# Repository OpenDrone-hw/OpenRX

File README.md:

# OpenRX

OpenRX is the home of the OpenDrone open-source ExpressLRS receiver family.
The four boards now follow the same one-board-per-repository standard as the
rest of the OpenDrone hardware line. This repository remains open as the
family hub, preserving its stars, issues, releases, tags, and complete history.

## Board repositories

| Board | Radio and antenna | Source and releases |
|---|---|---|
| OpenRX Lite | SX1281, 2.4 GHz, on-board ceramic | [OpenDrone-hw/OpenRX-Lite](https://github.com/OpenDrone-hw/OpenRX-Lite) |
| OpenRX Lite-UFL | SX1281, 2.4 GHz, U.FL | [OpenDrone-hw/OpenRX-Lite-UFL](https://github.com/OpenDrone-hw/OpenRX-Lite-UFL) |
| OpenRX Mono | LR1121, dual band, one U.FL | [OpenDrone-hw/OpenRX-Mono](https://github.com/OpenDrone-hw/OpenRX-Mono) |
| OpenRX Gemini | Two LR1121 radios, dual band, two U.FL | [OpenDrone-hw/OpenRX-Gemini](https://github.com/OpenDrone-hw/OpenRX-Gemini) |

KiCad sources, firmware target definitions, board documentation, and future
releases live in those repositories. The family-level Rev 2 and Rev 2.1 tags
and releases remain here as the immutable record of the original combined
repository; their per-board assets are also available from each board repo.
The Rev 2.2 tag marks the source of the production panel in `panel/`, the four
boards merged on one strip. Fab-ready manufacturing files are kept in a private
Incutec production repository and are not published.

## Specifications

| | Lite | Lite-UFL | Mono | Gemini |
|---|---|---|---|---|
| Band | 2.4 GHz | 2.4 GHz | Dual band | Dual band, Xrossband |
| Radio | SX1281 | SX1281 | LR1121 | 2x LR1121 |
| Antenna | On-board ceramic | U.FL | U.FL | 2x U.FL |
| Telemetry power | 13 dBm (20 mW) | 13 dBm (20 mW) | Up to 22 dBm (158 mW) | Up to 22 dBm (158 mW) |
| Protocol | CRSF | CRSF | CRSF | CRSF |
| MCU | ESP32-C3 | ESP32-C3 | ESP32-C3 | ESP32-C3 |
| Input | 5 V pad | 5 V pad | 5 V pad | 5 V pad |
| Firmware | ExpressLRS | ExpressLRS | ExpressLRS | ExpressLRS |
| Flashing | Betaflight passthrough or Wi-Fi | Betaflight passthrough or Wi-Fi | Betaflight passthrough or Wi-Fi | Betaflight passthrough or Wi-Fi |
| Dimensions | 10.0 x 11.5 mm | 10.0 x 11.5 mm | 10.0 x 17.3 mm | 17.0 x 15.7 mm |
| PCB | 6-layer, 1.0 mm | 6-layer, 1.0 mm | 6-layer, 1.0 mm | 6-layer, 1.0 mm |

OSHWA certification is issued per board:
[Lite BE000030](https://certification.oshwa.org/be000030.html),
[Lite-UFL BE000031](https://certification.oshwa.org/be000031.html),
[Mono BE000032](https://certification.oshwa.org/be000032.html), and
[Gemini BE000033](https://certification.oshwa.org/be000033.html).

## In the line

What pairs with what, and what is available:
[opendrone.be](https://opendrone.be).

## Contributing

Choose the board repository above for hardware changes. Family-wide questions
and historical discussion remain welcome here. See
[CONTRIBUTING.md](CONTRIBUTING.md).

## License

Hardware licensed under [CERN-OHL-S-2.0](https://ohwr.org/cern_ohl_s_v2.txt),
see [LICENSE](LICENSE).

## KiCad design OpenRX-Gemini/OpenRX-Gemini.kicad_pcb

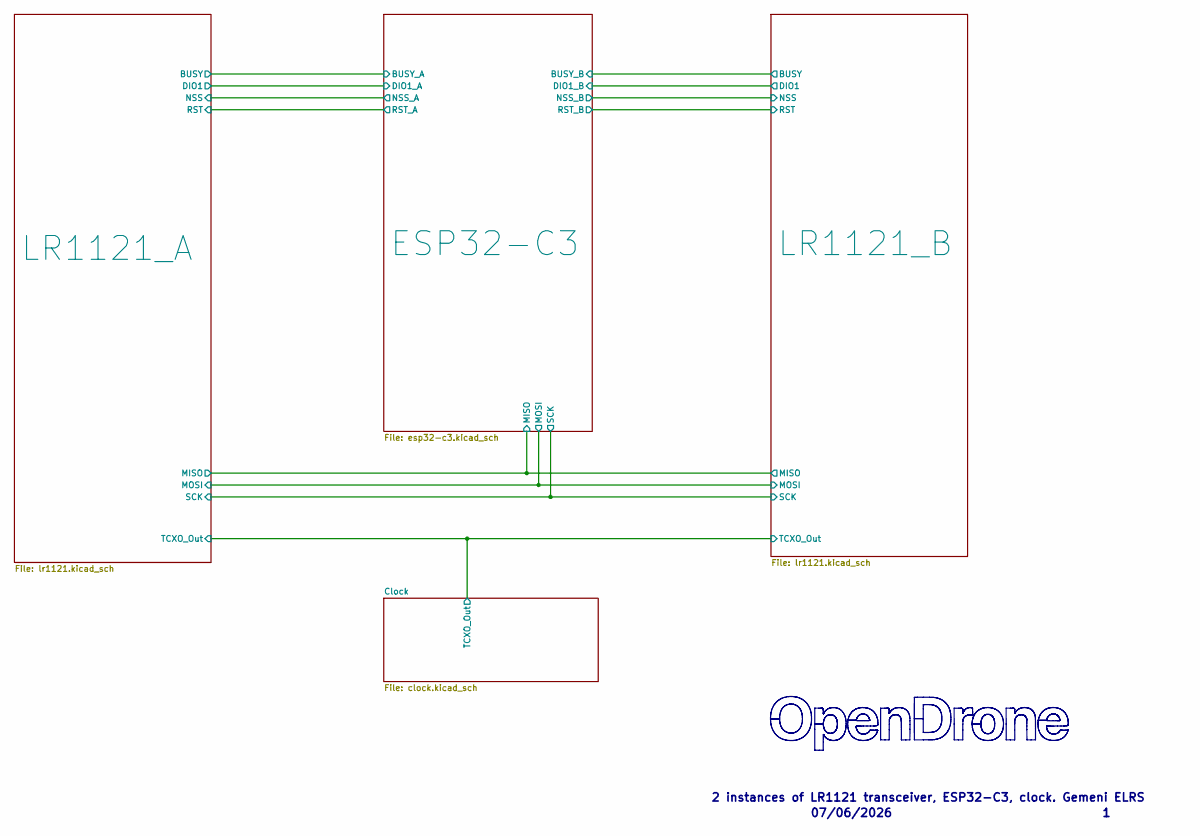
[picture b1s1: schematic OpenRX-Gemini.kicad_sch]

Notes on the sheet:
07/06/2026
2 instances of LR1121 transceiver, ESP32-C3, clock. Gemeni ELRS

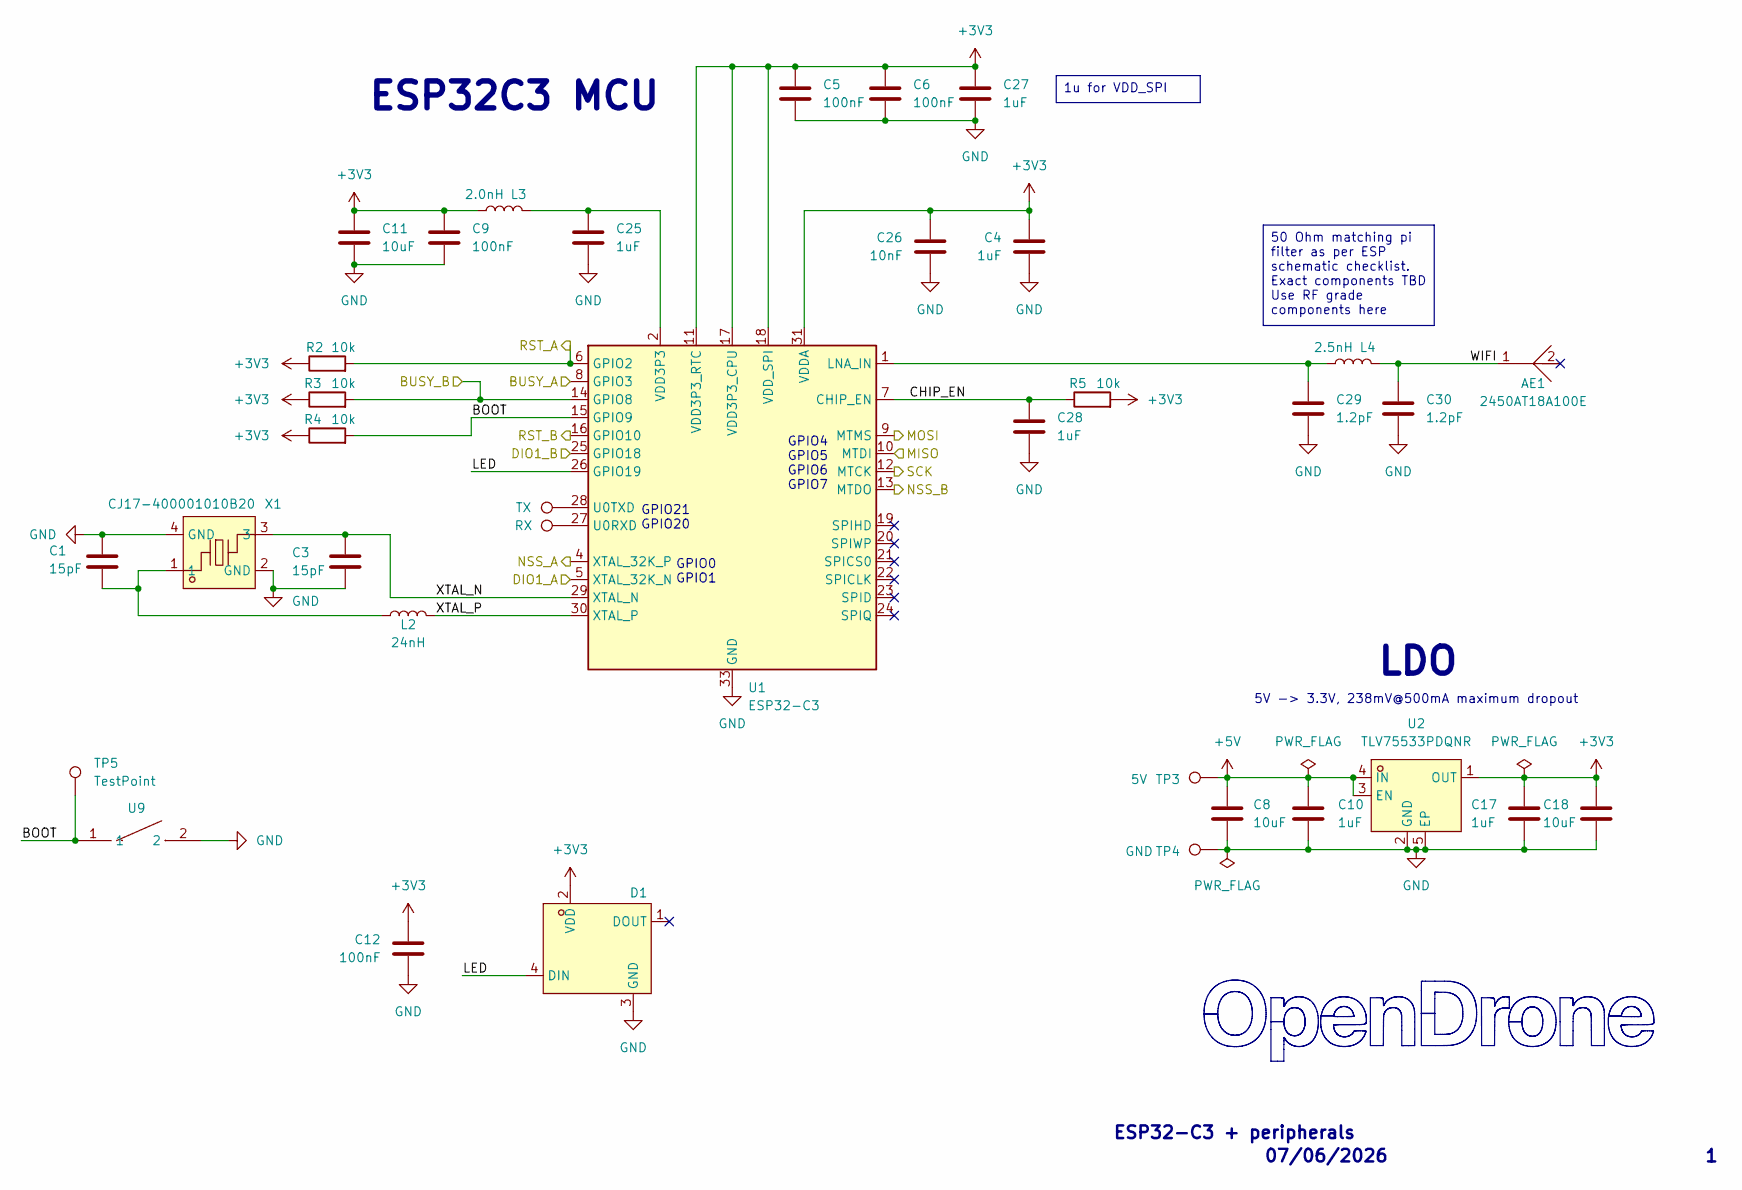
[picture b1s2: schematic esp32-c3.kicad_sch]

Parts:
AE1: 2450AT18A100E; ANT-SMD_L3.2-W1.6; MPN 2450AT18A100E; LCSC Part C89334
C1, C3: 15pF; C_0201_0603Metric; MPN GRM0335C1H150JA01D; LCSC C85891
C4, C10, C17, C25, C27, C28: 1uF; C_0201_0603Metric; MPN GRM033R61A105ME44D; LCSC C76935
C5, C6, C9, C12: 100nF; C_0201_0603Metric; MPN GRM033R61E104KE14D; LCSC C76939
C8, C18: 10uF; C_0402_1005Metric; MPN CL05A106MQ5NUNC; LCSC C15525
C11: 10uF; C_0402_1005Metric; MPN GRM155R60J106ME44D; LCSC C76991
C26: 10nF; C_0201_0603Metric; MPN GRM033R61A103KA01J; LCSC C2168164
C29, C30: 1.2pF; C_0201_0603Metric; MPN GRM0335C1H1R2BA01D; LCSC C85895
D1: XL-1010RGBC-WS2812B; LED-SMD_4P-L1.0-W1.0-TL_XL-1010RGBC-WS2812B; MPN XL-1010RGBC-2812B; LCSC C5349953
L2: 24nH; L_0201_0603Metric; MPN LQP03TN24NH02D; LCSC C206441
L3: 2.0nH; L_0201_0603Metric; MPN LQP03TN2N0B02D; LCSC C86125
L4: 2.5nH; L_0201_0603Metric; MPN LQP03TN2N5C02D; LCSC C206435
R2, R3, R4, R5: 10k; R_0201_0603Metric; MPN RC0201FR-0710KL; LCSC C106225
TP1: RX; SolderPad_1.2x2.0mm
TP2: TX; SolderPad_1.2x2.0mm
TP3: 5V; SolderPad_1.2x2.0mm
TP4: GND; SolderPad_1.2x2.0mm
TP5: TestPoint; TestPoint_Pad_D1.5mm
U1: ESP32-C3; QFN-32-1EP_5x5mm_P0.5mm_EP3.7x3.7mm
U2: TLV75533PDQNR; X2SON-4_L1.0-W1.0-P0.65-TL-EP; MPN TLV75533PDQNR; LCSC Part C2861882
U9: TS2306A 240GF MSM 9_C2976675; SW-SMD_4P-L3.0-W2.0-P0.85-LS3.5; MPN TS2306A 240gf MSM 9; LCSC C2976675
X1: CJ17-400001010B20; CRYSTAL-SMD_4P-L1.6-W1.2-BL; MPN CJ17-400001010B20; LCSC Part C2875272

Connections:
+3V3: C4.1, C5.1, C6.1, C9.1, C11.1, C12.1, C17.1, C18.1, C26.1, C27.1, D1.2 (VDD), L3.2, R2.1, R3.1, R4.1, R5.2, U1.11 (VDD3P3_RTC), U1.17 (VDD3P3_CPU), U1.18 (VDD_SPI), U1.31 (VDDA), U1.32 (VDDA), U2.1 (OUT); also elsewhere on the board
+5V: C8.1, C10.1, TP3.1 (1_1), U2.3 (EN), U2.4 (IN)
/ESP32-C3/BOOT: R4.2, TP5.1 (1_1), U1.15 (GPIO9), U9.1
/ESP32-C3/BUSY_A: U1.8 (GPIO3); also elsewhere on the board
/ESP32-C3/BUSY_B: R3.2, U1.14 (GPIO8); also elsewhere on the board
/ESP32-C3/CHIP_EN: C28.1, R5.1, U1.7 (CHIP_EN)
/ESP32-C3/DIO1_A: U1.5 (XTAL_32K_N); also elsewhere on the board
/ESP32-C3/DIO1_B: U1.25 (GPIO18); also elsewhere on the board
/ESP32-C3/LED: D1.4 (DIN), U1.26 (GPIO19)
/ESP32-C3/MISO: U1.10 (MTDI); also elsewhere on the board
/ESP32-C3/MOSI: U1.9 (MTMS); also elsewhere on the board
/ESP32-C3/NSS_A: U1.4 (XTAL_32K_P); also elsewhere on the board
/ESP32-C3/NSS_B: U1.13 (MTDO); also elsewhere on the board
/ESP32-C3/RST_A: R2.2, U1.6 (GPIO2); also elsewhere on the board
/ESP32-C3/RST_B: U1.16 (GPIO10); also elsewhere on the board
/ESP32-C3/SCK: U1.12 (MTCK); also elsewhere on the board
/ESP32-C3/WIFI: AE1.1, C30.1, L4.1
/ESP32-C3/XTAL_N: C3.1, U1.29 (XTAL_N), X1.3
/ESP32-C3/XTAL_P: L2.2, U1.30 (XTAL_P)
GND: C1.2, C3.2, C4.2, C5.2, C6.2, C8.2, C9.2, C10.2, C11.2, C12.2, C17.2, C18.2, C25.2, C26.2, C27.2, C28.2, C29.2, C30.2, D1.3 (GND), TP4.1 (1_1), U1.33 (GND), U2.2 (GND), U2.5 (EP), U9.2, X1.2 (GND), X1.4 (GND); also elsewhere on the board
unnamed: C1.1, L2.1, X1.1
unnamed: C25.1, L3.1, U1.2 (VDD3P3), U1.3 (VDD3P3)
unnamed: C29.1, L4.2, U1.1 (LNA_IN)
unnamed: TP1.1 (1_1), U1.27 (U0RXD)
unnamed: TP2.1 (1_1), U1.28 (U0TXD)

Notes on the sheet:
ESP32C3 MCU
07/06/2026
GPIO21 GPIO20
GPIO0 GPIO1
5V -> 3.3V, 238mV@500mA maximum dropout
GPIO4 GPIO5 GPIO6 GPIO7
LDO
ESP32-C3 + peripherals
50 Ohm matching pi filter as per ESP schematic checklist. Exact components TBD Use RF grade components here
1u for VDD_SPI

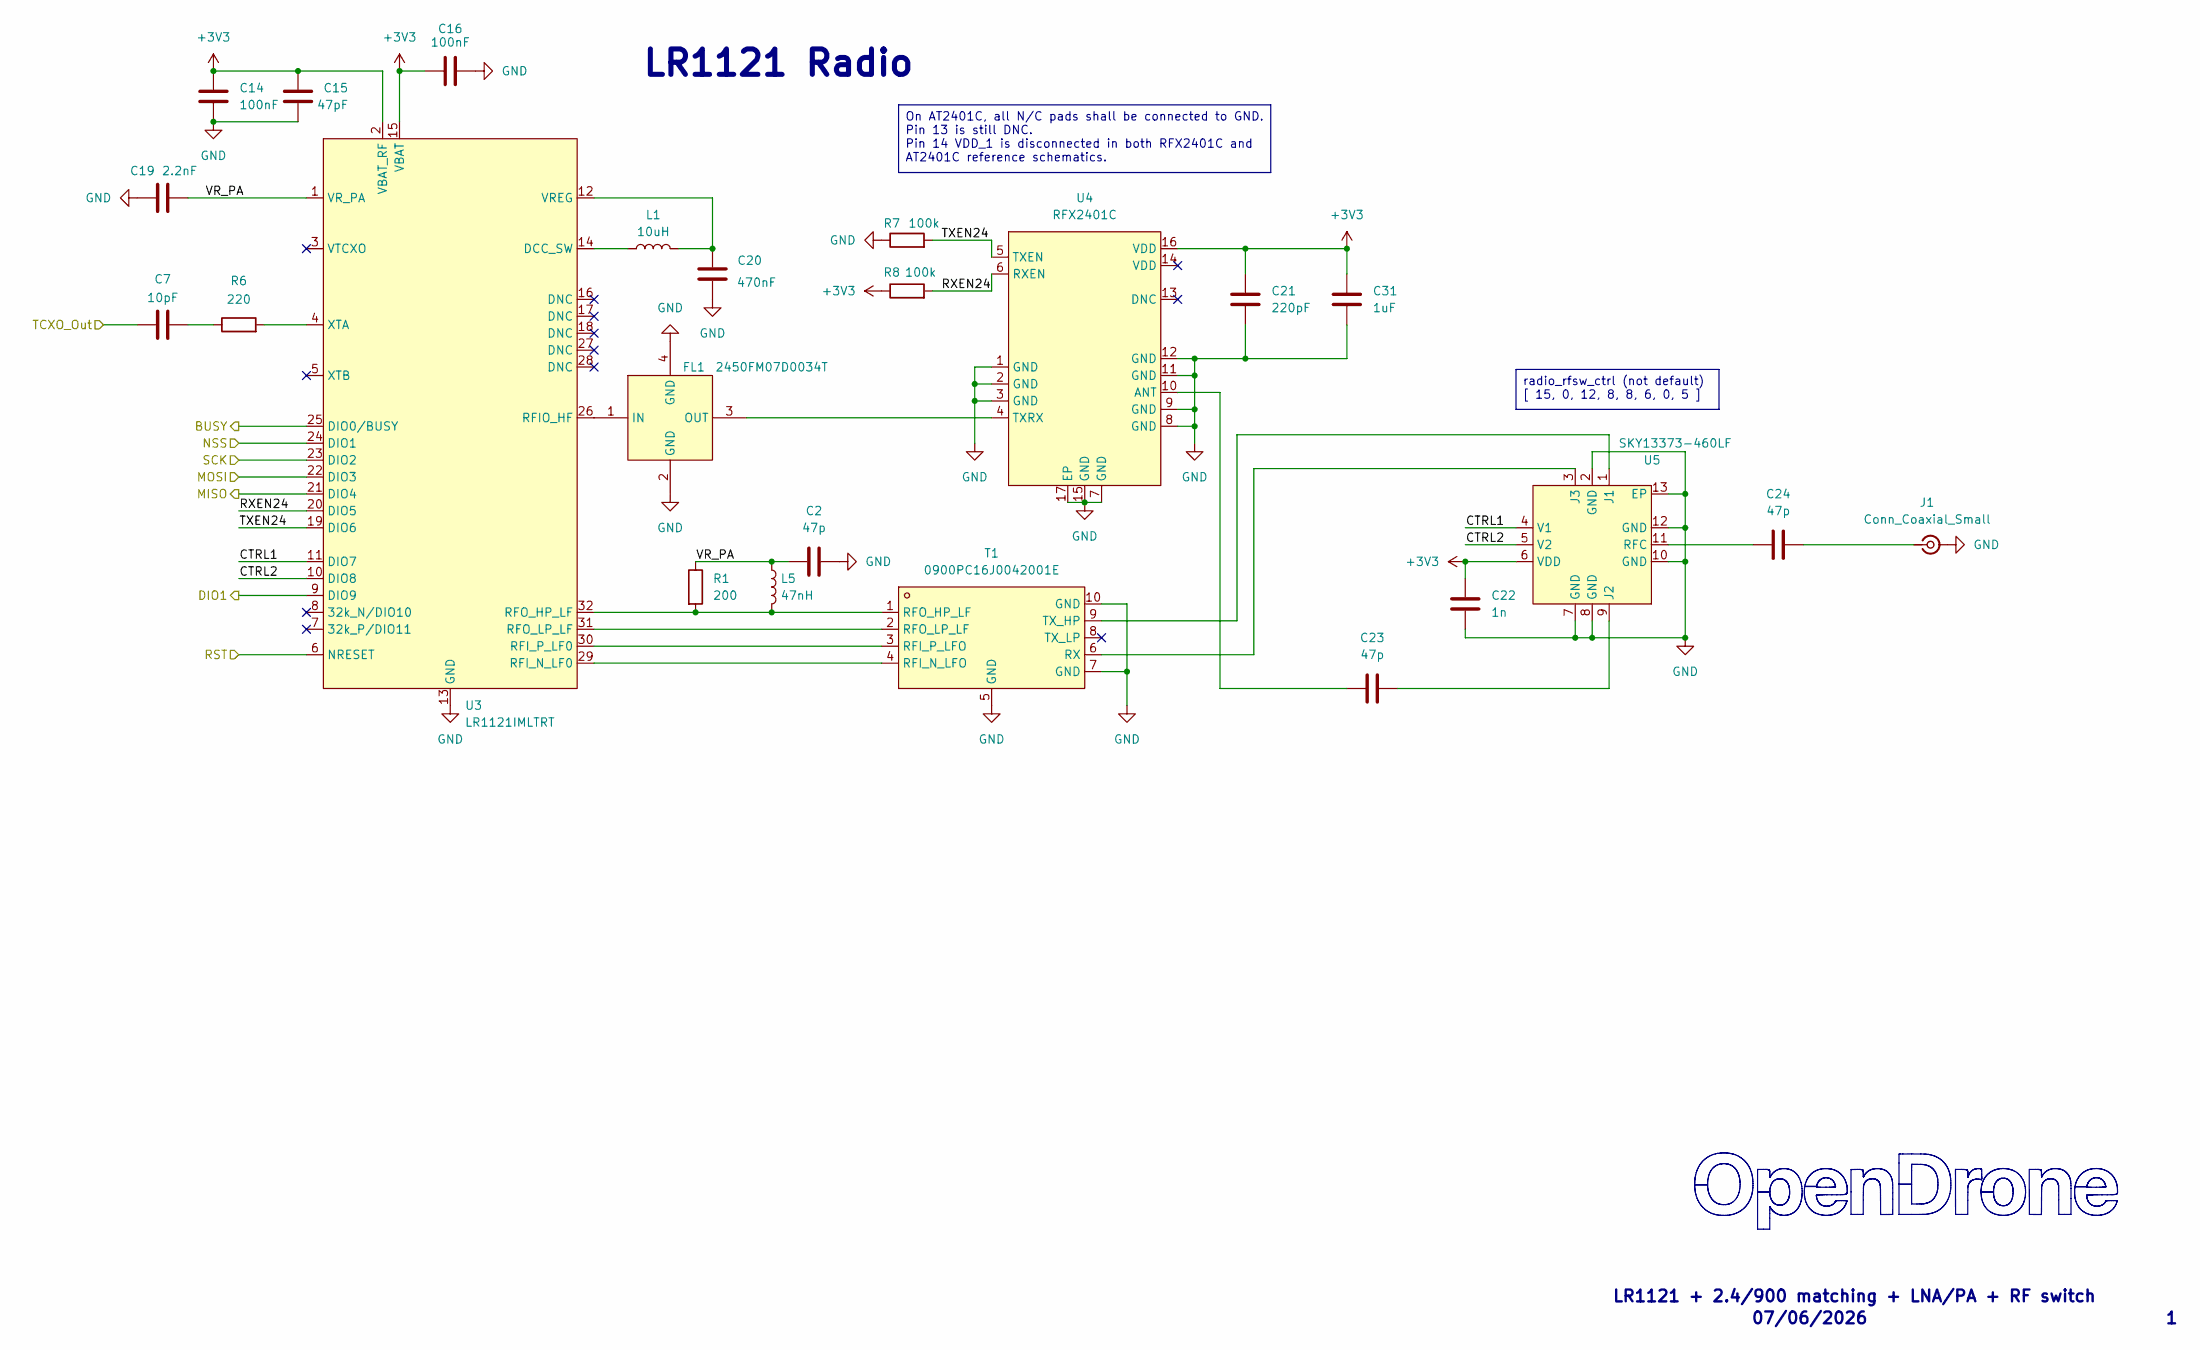
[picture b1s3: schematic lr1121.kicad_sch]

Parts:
C2, C23, C24: 47p; C_0201_0603Metric; MPN GRM0335C1H470JA01D; LCSC C85908
C7: 10pF; C_0201_0603Metric; MPN GRM0335C1H100FA01D; LCSC C384956
C14, C16: 100nF; C_0201_0603Metric; MPN GRM033R61E104KE14D; LCSC C76939
C15: 47pF; C_0201_0603Metric; MPN GRM0335C1H470JA01D; LCSC C85908
C19: 2.2nF; C_0201_0603Metric; MPN GRM033R71E222KA12D; LCSC C161488
C20: 470nF; C_0201_0603Metric; MPN GRM033R60J474KE90D; LCSC C85926
C21: 220pF; C_0201_0603Metric; MPN GRM0335C1E221JA01D; LCSC C907939
C22: 1n; C_0201_0603Metric; MPN GRM033R71H102KA12D; LCSC C85934
C31: 1uF; C_0201_0603Metric; MPN GRM033R61A105ME44D; LCSC C76935
FL1: 2450FM07D0034T; FILTER-SMD_4P-L1.0-W0.5-L; MPN 2450FM07D0034T; LCSC Part_1 C2651081
J1: Conn_Coaxial_Small; U.FL_Hirose_U.FL-R-SMT-1_Vertical; MPN U.FL-R-SMT-1(80); LCSC C88374
L1: 10uH; L_0603_1608Metric; MPN MLZ1608N100LT000; LCSC C194437
L5: 47nH; L_0402_1005Metric; MPN LQW15AN47NJ00D; LCSC C192855
R1: 200; R_0201_0603Metric; MPN RC0201FR-07200RL; LCSC C274337
R6: 220; R_0201_0603Metric; MPN ERJ-1GNF2200C; LCSC C2074788
R7, R8: 100k; R_0201_0603Metric; MPN RC0201FR-07100KL; LCSC C106224
T1: 0900PC16J0042001E; FILTER-SMD_10P-L2.0-W1.6-BL; MPN 0900PC16J0042001E; LCSC C19842466
U3: LR1121IMLTRT; QFN-32-1EP_5x5mm_P0.5mm_EP3.7x3.7mm; MPN LR1121IMLTRT; LCSC C7498014
U4: RFX2401C; QFN-16_L3.0-W3.0-P0.50-BL-EP1.7; MPN RFX2401C; LCSC C19213
U5: SKY13373-460LF; QFN-12_EP_2x2_Pitch0.5mm

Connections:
+3V3: C14.1, C15.1, C16.1, C21.1, C22.1, C31.1, R8.1, U3.2 (VBAT_RF), U3.15 (VBAT), U4.16 (VDD), U5.6 (VDD); also elsewhere on the board
/Clock/TCXO_Out: C7.2; also elsewhere on the board
/ESP32-C3/BUSY_A: U3.25 (DIO0/BUSY); also elsewhere on the board
/ESP32-C3/DIO1_A: U3.9 (DIO9); also elsewhere on the board
/ESP32-C3/MISO: U3.21 (DIO4); also elsewhere on the board
/ESP32-C3/MOSI: U3.22 (DIO3); also elsewhere on the board
/ESP32-C3/NSS_A: U3.24 (DIO1); also elsewhere on the board
/ESP32-C3/RST_A: U3.6 (NRESET); also elsewhere on the board
/ESP32-C3/SCK: U3.23 (DIO2); also elsewhere on the board
/LR1121_A/CTRL1: U3.11 (DIO7), U5.4 (V1)
/LR1121_A/CTRL2: U3.10 (DIO8), U5.5 (V2)
/LR1121_A/RXEN24: R8.2, U3.20 (DIO5), U4.6 (RXEN)
/LR1121_A/TXEN24: R7.2, U3.19 (DIO6), U4.5 (TXEN)
/LR1121_A/VR_PA: C2.1, C19.1, L5.1, R1.1, U3.1 (VR_PA)
GND: C2.2, C14.2, C15.2, C16.2, C19.2, C20.1, C21.2, C22.2, C31.2, FL1.2 (GND), FL1.4 (GND), J1.2 (Ext), R7.1, T1.5 (GND), T1.7 (GND), T1.10 (GND), U3.13 (GND), U3.33 (EP), U4.1 (GND), U4.2 (GND), U4.3 (GND), U4.7 (GND), U4.8 (GND), U4.9 (GND), U4.11 (GND), U4.12 (GND), U4.15 (GND), U4.17 (EP), U5.2 (GND), U5.7 (GND), U5.8 (GND), U5.10 (GND), U5.12 (GND), U5.13 (EP); also elsewhere on the board
unnamed: C7.1, R6.1
unnamed: FL1.1 (IN), U3.26 (RFIO_HF)
unnamed: FL1.3 (OUT), U4.4 (TXRX)
unnamed: C24.2, J1.1 (In)
unnamed: T1.4 (RFI_N_LFO), U3.29 (RFI_N_LF0)
unnamed: T1.3 (RFI_P_LFO), U3.30 (RFI_P_LF0)
unnamed: L5.2, R1.2, T1.1 (RFO_HP_LF), U3.32 (RFO_HP_LF)
unnamed: T1.2 (RFO_LP_LF), U3.31 (RFO_LP_LF)
unnamed: T1.6 (RX), U5.3 (J3)
unnamed: T1.9 (TX_HP), U5.1 (J1)
unnamed: L1.1, U3.14 (DCC_SW)
unnamed: C20.2, L1.2, U3.12 (VREG)
unnamed: R6.2, U3.4 (XTA)
unnamed: C23.1, U4.10 (ANT)
unnamed: C23.2, U5.9 (J2)
unnamed: C24.1, U5.11 (RFC)

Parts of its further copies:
C33: 2.2nF; C_0201_0603Metric; MPN GRM033R71E222KA12D; LCSC C161488
C34: 10pF; C_0201_0603Metric; MPN GRM0335C1H100FA01D; LCSC C384956
C35, C37: 100nF; C_0201_0603Metric; MPN GRM033R61E104KE14D; LCSC C76939
C36: 47pF; C_0201_0603Metric; MPN GRM0335C1H470JA01D; LCSC C85908
C38: 470nF; C_0201_0603Metric; MPN GRM033R60J474KE90D; LCSC C85926
C39, C42, C44: 47p; C_0201_0603Metric; MPN GRM0335C1H470JA01D; LCSC C85908
C40: 220pF; C_0201_0603Metric; MPN GRM0335C1E221JA01D; LCSC C907939
C41: 1uF; C_0201_0603Metric; MPN GRM033R61A105ME44D; LCSC C76935
C43: 1n; C_0201_0603Metric; MPN GRM033R71H102KA12D; LCSC C85934
FL2: 2450FM07D0034T; FILTER-SMD_4P-L1.0-W0.5-L; MPN 2450FM07D0034T; LCSC Part_1 C2651081
J2: Conn_Coaxial_Small; U.FL_Hirose_U.FL-R-SMT-1_Vertical; MPN U.FL-R-SMT-1(80); LCSC C88374
L6: 10uH; L_0603_1608Metric; MPN MLZ1608N100LT000; LCSC C194437
L7: 47nH; L_0402_1005Metric; MPN LQW15AN47NJ00D; LCSC C192855
R9: 220; R_0201_0603Metric; MPN ERJ-1GNF2200C; LCSC C2074788
R10: 200; R_0201_0603Metric; MPN RC0201FR-07200RL; LCSC C274337
R11, R12: 100k; R_0201_0603Metric; MPN RC0201FR-07100KL; LCSC C106224
T2: 0900PC16J0042001E; FILTER-SMD_10P-L2.0-W1.6-BL; MPN 0900PC16J0042001E; LCSC C19842466
U6: LR1121IMLTRT; QFN-32-1EP_5x5mm_P0.5mm_EP3.7x3.7mm; MPN LR1121IMLTRT; LCSC C7498014
U7: RFX2401C; QFN-16_L3.0-W3.0-P0.50-BL-EP1.7; MPN RFX2401C; LCSC C19213
U8: SKY13373-460LF; QFN-12_EP_2x2_Pitch0.5mm

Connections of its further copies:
+3V3: C35.1, C36.1, C37.1, C40.1, C41.1, C43.1, R12.1, U6.2 (VBAT_RF), U6.15 (VBAT), U7.16 (VDD), U8.6 (VDD); also elsewhere on the board
/Clock/TCXO_Out: C34.2; also elsewhere on the board
/ESP32-C3/BUSY_B: U6.25 (DIO0/BUSY); also elsewhere on the board
/ESP32-C3/DIO1_B: U6.9 (DIO9); also elsewhere on the board
/ESP32-C3/MISO: U6.21 (DIO4); also elsewhere on the board
/ESP32-C3/MOSI: U6.22 (DIO3); also elsewhere on the board
/ESP32-C3/NSS_B: U6.24 (DIO1); also elsewhere on the board
/ESP32-C3/RST_B: U6.6 (NRESET); also elsewhere on the board
/ESP32-C3/SCK: U6.23 (DIO2); also elsewhere on the board
/LR1121_B/CTRL1: U6.11 (DIO7), U8.4 (V1)
/LR1121_B/CTRL2: U6.10 (DIO8), U8.5 (V2)
/LR1121_B/RXEN24: R12.2, U6.20 (DIO5), U7.6 (RXEN)
/LR1121_B/TXEN24: R11.2, U6.19 (DIO6), U7.5 (TXEN)
/LR1121_B/VR_PA: C33.1, C39.1, L7.1, R10.1, U6.1 (VR_PA)
GND: C33.2, C35.2, C36.2, C37.2, C38.1, C39.2, C40.2, C41.2, C43.2, FL2.2 (GND), FL2.4 (GND), J2.2 (Ext), R11.1, T2.5 (GND), T2.7 (GND), T2.10 (GND), U6.13 (GND), U6.33 (EP), U7.1 (GND), U7.2 (GND), U7.3 (GND), U7.7 (GND), U7.8 (GND), U7.9 (GND), U7.11 (GND), U7.12 (GND), U7.15 (GND), U7.17 (EP), U8.2 (GND), U8.7 (GND), U8.8 (GND), U8.10 (GND), U8.12 (GND), U8.13 (EP); also elsewhere on the board
unnamed: C34.1, R9.1
unnamed: FL2.1 (IN), U6.26 (RFIO_HF)
unnamed: FL2.3 (OUT), U7.4 (TXRX)
unnamed: C44.2, J2.1 (In)
unnamed: T2.4 (RFI_N_LFO), U6.29 (RFI_N_LF0)
unnamed: T2.3 (RFI_P_LFO), U6.30 (RFI_P_LF0)
unnamed: L7.2, R10.2, T2.1 (RFO_HP_LF), U6.32 (RFO_HP_LF)
unnamed: T2.2 (RFO_LP_LF), U6.31 (RFO_LP_LF)
unnamed: T2.6 (RX), U8.3 (J3)
unnamed: T2.9 (TX_HP), U8.1 (J1)
unnamed: L6.1, U6.14 (DCC_SW)
unnamed: C38.2, L6.2, U6.12 (VREG)
unnamed: R9.2, U6.4 (XTA)
unnamed: C42.1, U7.10 (ANT)
unnamed: C42.2, U8.9 (J2)
unnamed: C44.1, U8.11 (RFC)

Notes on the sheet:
LR1121 + 2.4/900 matching + LNA/PA + RF switch
LR1121 Radio
07/06/2026
radio_rfsw_ctrl (not default) [ 15, 0, 12, 8, 8, 6, 0, 5 ]
On AT2401C, all N/C pads shall be connected to GND. Pin 13 is still DNC. Pin 14 VDD_1 is disconnected in both RFX2401C and AT2401C reference schematics.

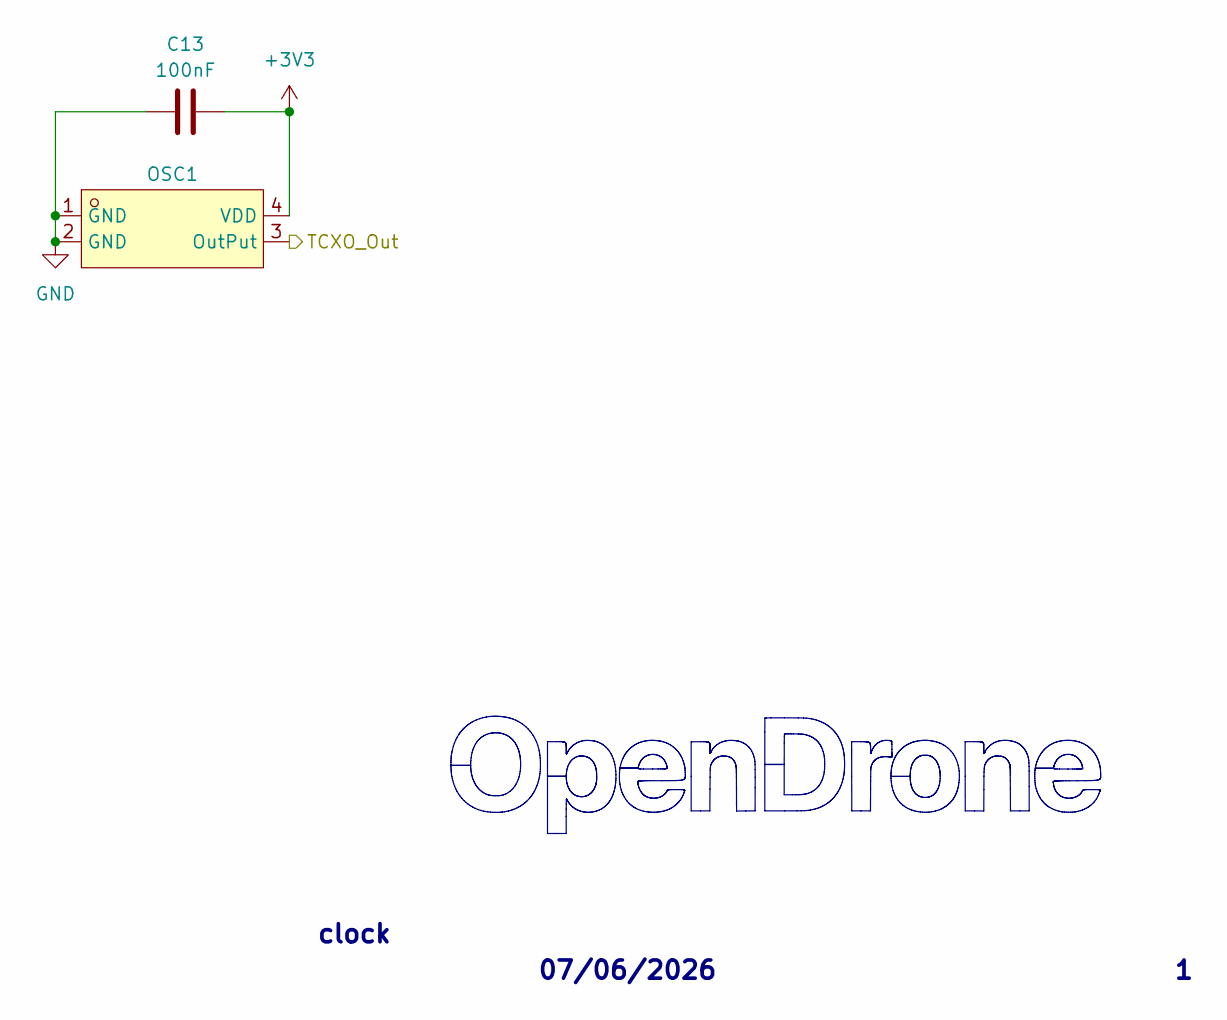
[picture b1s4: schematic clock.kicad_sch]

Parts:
C13: 100nF; C_0201_0603Metric; MPN GRM033R61E104KE14D; LCSC C76939
OSC1: OW7EL89CENUYO3YLC-32M; OSC-SMD_4P-L2.0-W1.6-BL_TXC_7Z; MPN OW7EL89CENUYO3YLC-32M; LCSC C22381772

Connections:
+3V3: C13.2, OSC1.4 (VDD); also elsewhere on the board
/Clock/TCXO_Out: OSC1.3 (OutPut); also elsewhere on the board
GND: C13.1, OSC1.1 (GND), OSC1.2 (GND); also elsewhere on the board

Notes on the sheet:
07/06/2026
clock

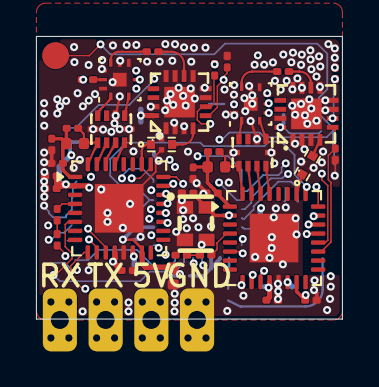
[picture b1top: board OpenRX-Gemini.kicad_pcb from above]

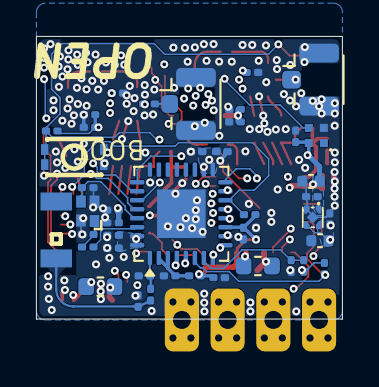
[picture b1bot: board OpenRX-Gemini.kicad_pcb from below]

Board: 6 copper layers, 17.0 x 15.7 mm, 86 parts (44 on the bottom side), 68 nets.

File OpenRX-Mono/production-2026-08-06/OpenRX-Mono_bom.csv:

"Designator","Comment","Footprint","Qty","LCSC Part #"
"AE1","2450AT18A100E","OpenRX-Shared:ANT-SMD_L3.2-W1.6","1","C89334"
"C1,C3","15pF","Capacitor_SMD:C_0201_0603Metric","2","C85891"
"C2,C23,C24","47p","Capacitor_SMD:C_0201_0603Metric","3","C85908"
"C4,C10,C17,C25,C27,C28,C31","1uF","Capacitor_SMD:C_0201_0603Metric","7","C76935"
"C5,C6,C9,C12,C13,C14,C16","100nF","Capacitor_SMD:C_0201_0603Metric","7","C76939"
"C7","10pF","Capacitor_SMD:C_0201_0603Metric","1","C384956"
"C8,C18","10uF","Capacitor_SMD:C_0402_1005Metric","2","C15525"
"C11","10uF","Capacitor_SMD:C_0402_1005Metric","1","C76991"
"C15","47pF","Capacitor_SMD:C_0201_0603Metric","1","C85908"
"C19","2.2nF","Capacitor_SMD:C_0201_0603Metric","1","C161488"
"C20","470nF","Capacitor_SMD:C_0201_0603Metric","1","C85926"
"C21","220pF","Capacitor_SMD:C_0201_0603Metric","1","C907939"
"C22","1n","Capacitor_SMD:C_0201_0603Metric","1","C85934"
"C26","10nF","Capacitor_SMD:C_0201_0603Metric","1","C2168164"
"C29,C30","1.2pF","Capacitor_SMD:C_0201_0603Metric","2","C85895"
"D1","XL-1010RGBC-WS2812B","OpenRX-Shared:LED-SMD_4P-L1.0-W1.0-TL_XL-1010RGBC-WS2812B","1",""
"FL1","2450FM07D0034T","OpenRX-Shared:FILTER-SMD_4P-L1.0-W0.5-L","1",""
"J1","Conn_Coaxial_Small","Connector_Coaxial:U.FL_Hirose_U.FL-R-SMT-1_Vertical","1","C88374"
"L1","10uH","Inductor_SMD:L_0603_1608Metric","1","C194437"
"L2","24nH","Inductor_SMD:L_0201_0603Metric","1","C206441"
"L3","2.0nH","Inductor_SMD:L_0201_0603Metric","1","C86125"
"L4","2.5nH","Inductor_SMD:L_0201_0603Metric","1","C206435"
"L5","47nH","Inductor_SMD:L_0402_1005Metric","1","C192855"
"OSC1","OW7EL89CENUYO3YLC-32M","OpenRX-Shared:OSC-SMD_4P-L2.0-W1.6-BL_TXC_7Z","1",""
"R1","200","Resistor_SMD:R_0201_0603Metric","1","C274337"
"R2,R3,R4,R5","10k","Resistor_SMD:R_0201_0603Metric","4","C106225"
"R6","220","Resistor_SMD:R_0201_0603Metric","1","C2074788"
"R7,R8","100k","Resistor_SMD:R_0201_0603Metric","2","C106224"
"T1","0900PC16J0042001E","OpenRX-Shared:FILTER-SMD_10P-L2.0-W1.6-BL","1",""
"TP1","RX","OpenRX-Shared:SolderPad_1.2x2.0mm","1",""
"TP2","TX","OpenRX-Shared:SolderPad_1.2x2.0mm","1",""
"TP3","5V","OpenRX-Shared:SolderPad_1.2x2.0mm","1",""
"TP4","GND","OpenRX-Shared:SolderPad_1.2x2.0mm","1",""
"TP5","BOOT","OpenRX-Shared:SolderPad_1.2x2.0mm","1",""
"U1","ESP32-C3","Package_DFN_QFN:QFN-32-1EP_5x5mm_P0.5mm_EP3.7x3.7mm","1",""
"U2","TLV75533PDQNR","OpenRX-Shared:X2SON-4_L1.0-W1.0-P0.65-TL-EP","1","C2861882"
"U3","LR1121IMLTRT","Package_DFN_QFN:QFN-32-1EP_5x5mm_P0.5mm_EP3.7x3.7mm","1",""
"U4","RFX2401C","OpenRX-Shared:QFN-16_L3.0-W3.0-P0.50-BL-EP1.7","1",""
"U5","SKY13373-460LF","OpenRX-Shared:QFN-12_EP_2x2_Pitch0.5mm","1",""
"X1","CJ17-400001010B20","OpenRX-Shared:CRYSTAL-SMD_4P-L1.6-W1.2-BL","1","C2875272"

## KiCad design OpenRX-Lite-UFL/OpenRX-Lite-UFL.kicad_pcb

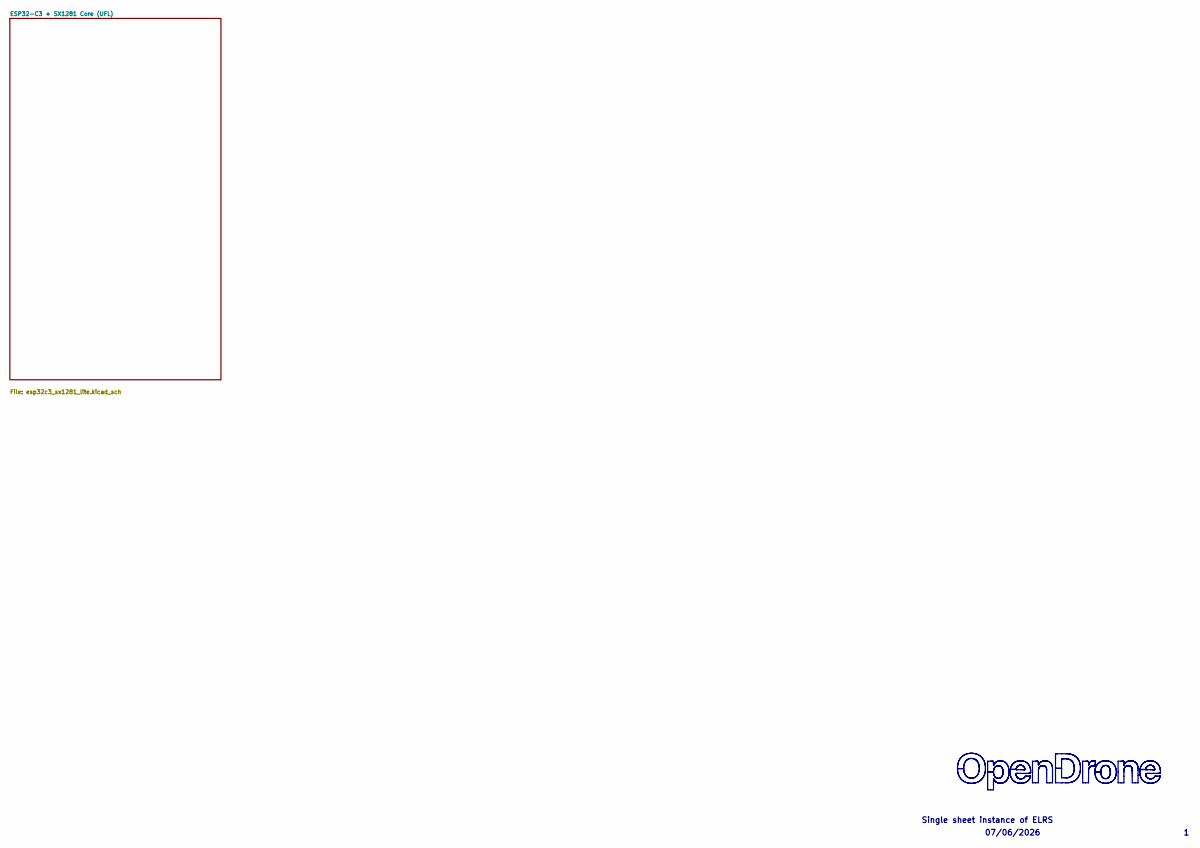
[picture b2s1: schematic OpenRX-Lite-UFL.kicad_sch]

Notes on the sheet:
07/06/2026
Single sheet instance of ELRS
